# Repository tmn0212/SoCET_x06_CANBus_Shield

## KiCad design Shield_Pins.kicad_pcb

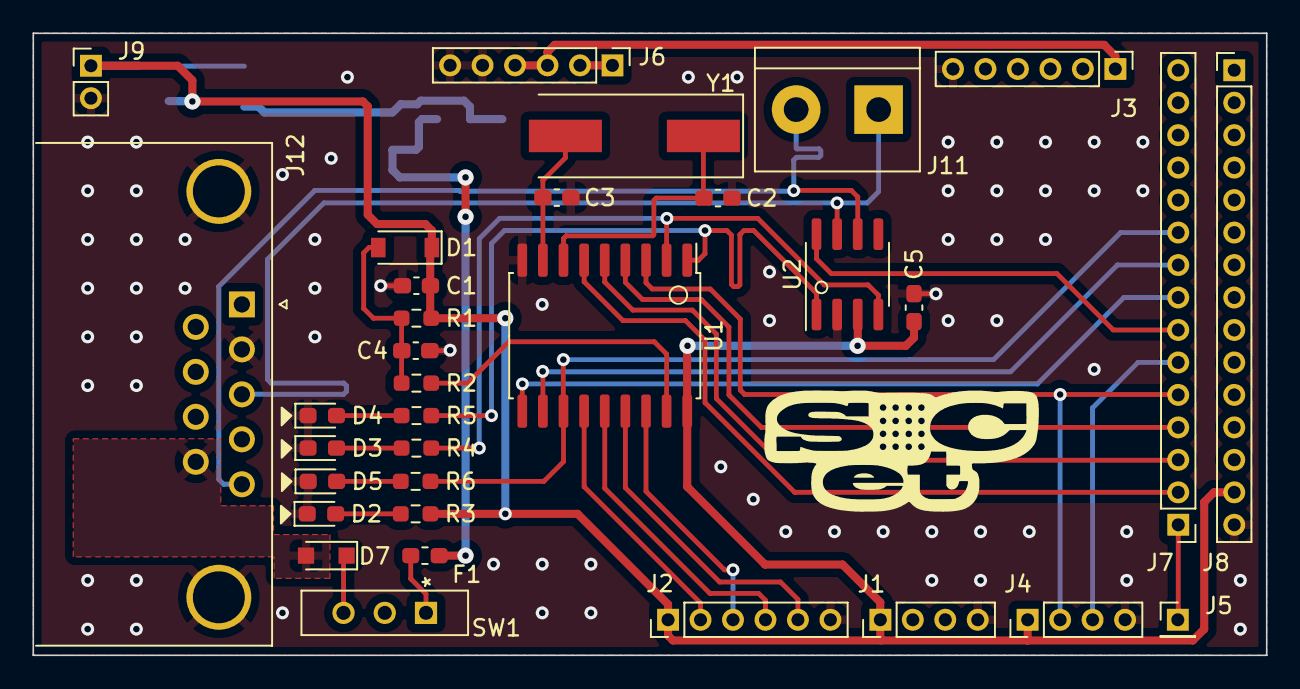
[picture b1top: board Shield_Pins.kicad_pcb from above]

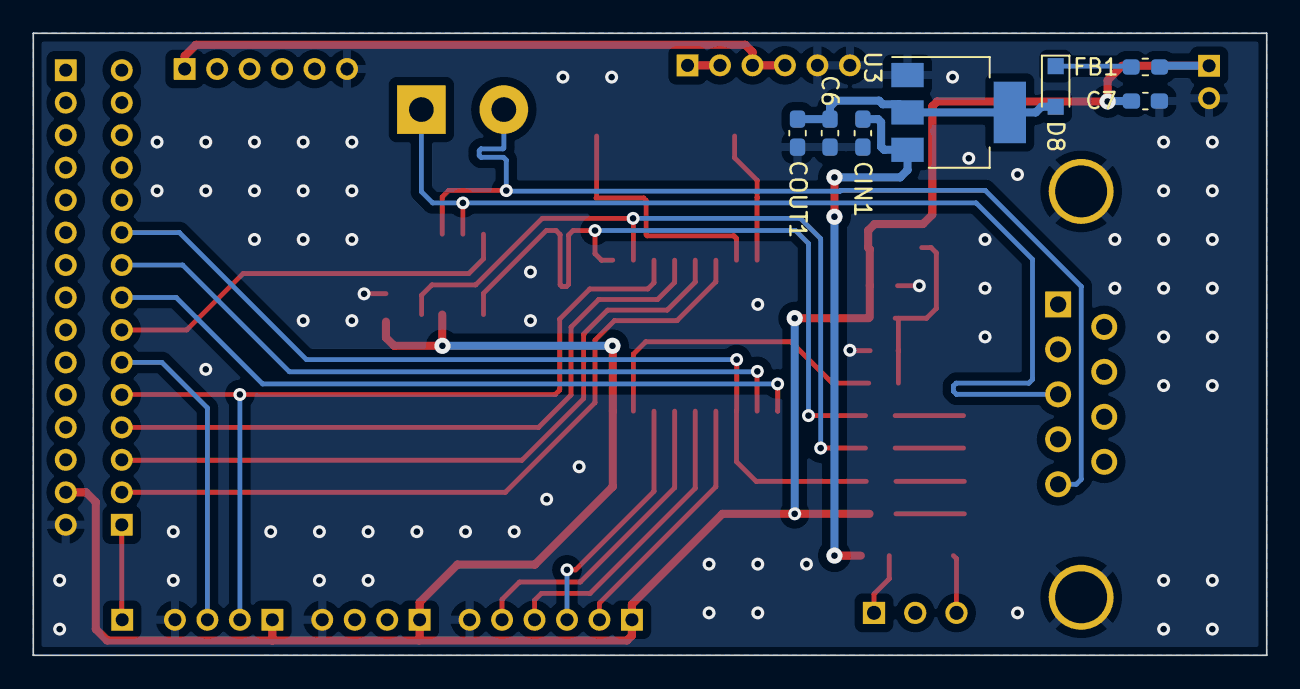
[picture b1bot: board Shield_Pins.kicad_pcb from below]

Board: 2 copper layers, 76.0 x 38.3 mm, 40 parts (7 on the bottom side), 36 nets.

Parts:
C1, C5: 0.1uF; C_0603_1608Metric_Pad1.08x0.95mm_HandSolder
C2, C3: 22pF; C_0603_1608Metric_Pad1.08x0.95mm_HandSolder
C4: 100pF; C_0603_1608Metric_Pad1.08x0.95mm_HandSolder
C6, C7: 100nF; C_0603_1608Metric_Pad1.08x0.95mm_HandSolder
CIN1: 100nF; C_0603_1608Metric_Pad1.08x0.95mm_HandSolder
COUT1: 10uF; C_0603_1608Metric_Pad1.08x0.95mm_HandSolder
D1: 3.3V 500mW; D_SOD-123
D2, D3, D4, D5: LED; LED_0603_1608Metric_Pad1.05x0.95mm_HandSolder
D7, D8: BAT165AX; D_SOD-323_HandSoldering
F1: 1.5A Fuse; Fuse_0603_1608Metric_Pad1.05x0.95mm_HandSolder
FB1: 120R; L_0603_1608Metric_Pad1.05x0.95mm_HandSolder
J1, J4: Conn_01x04_Male; PinHeader_1x04_P2.00mm_Vertical
J2, J3, J6: Conn_01x06_Male; PinHeader_1x06_P2.00mm_Vertical
J5: Conn_01x01_Male; PinHeader_1x01_P2.00mm_Vertical
J7, J8: Conn_01x15_Male; PinHeader_1x15_P2.00mm_Vertical
J9: Conn_01x02_Male; PinHeader_1x02_P2.00mm_Vertical
J11: Screw_Terminal_01x02; TerminalBlock_bornier-2_P5.08mm
J12: DB9_Male; DSUB-9_Male_Horizontal_P2.77x2.84mm_EdgePinOffset9.90mm_Hou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
R1: 6.3kR; R_0603_1608Metric_Pad0.98x0.95mm_HandSolder
R2: 1kR; R_0603_1608Metric_Pad0.98x0.95mm_HandSolder
R3, R4, R5, R6: 100R; R_0603_1608Metric_Pad0.98x0.95mm_HandSolder
SW1: SW_SPDT; 09.03290.01 switch
U1: MCP2515-xSO; SOIC-18W_7.5x11.6mm_P1.27mm
U2: MCP2551-I-SN; SOIC-8_3.9x4.9mm_P1.27mm
U3: LD1117S50TR_SOT223; SOT-223-3_TabPin2
Y1: 8MHz Crystal; Crystal_SMD_HC49-SD

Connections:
5V_OBD: C6.1, COUT1.1, D8.2 (A), U3.2 (VO)
12V_OBD: CIN1.1, F1.2, U3.3 (VI)
12V_OBD_IN: D7.2 (A), J12.9
+1V8: J6.1, J6.2
+3.3V: J3.1, J6.3, J6.4
+5V: C1.1, C5.1, C7.1, D1.1 (K), FB1.2, J1.1, J2.1, J4.1, J8.14, J9.1, R1.1, R3.1, U1.18 (VDD), U2.3 (VDD)
CANH: J11.1, J12.3, U2.7 (CANH)
CANL: J11.2, J12.5, U2.6 (CANL)
GND: C1.2, C2.2, C3.2, C4.2, C5.2, C6.2, C7.2, CIN1.2, COUT1.2, D2.1 (K), D3.1 (K), D4.1 (K), D5.1 (K), J1.4, J2.6, J3.6, J4.4, J6.5, J6.6, J8.15, J9.2, J12.2, U1.9 (VSS), U2.2 (VSS), U3.1 (GND)
IO7: J5.1, J7.1
IO8: J7.2, U1.6 (~TX2RTS)
IO9: J7.3, U1.5 (~TX1RTS)
IO10: J7.4, U1.4 (~TX0RTS)
IO11: J4.2, J7.5, U1.3 (CLKOUT/SOF)
IO12: J4.3, J7.6
IO17: J7.7, U2.8 (Rs)
IO18: J7.8, U1.10 (~RX1BF)
IO19: J7.9, U1.11 (~RX0BF)
IO20: J7.10, R6.1, U1.12 (~INT)
IO.CSB: J2.3, U1.16 (~CS)
IO.SCK: J2.2, U1.13 (SCK)
IO.SDI: J2.4, U1.14 (SI)
IO.SDO: J2.5, U1.15 (SO)
unnamed: C4.1, D1.2 (A), R1.2, R2.1
unnamed: D2.2 (A), R3.2
unnamed: D3.2 (A), R4.2
unnamed: D4.2 (A), R5.2
unnamed: D5.2 (A), R6.2
unnamed: D7.1 (K), SW1.2 (B)
unnamed: D8.1 (K), FB1.1
unnamed: F1.1, SW1.3 (C)
OSC1: C3.1, U1.8 (OSC1), Y1.2
OSC2: C2.1, U1.7 (OSC2), Y1.1
RXCAN: R4.1, U1.2 (RXCAN), U2.4 (RXD)
TXCAN: R5.1, U1.1 (TXCAN), U2.1 (TXD)
~CAN_RST: R2.2, U1.17 (~RESET)

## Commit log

2023-02-04 Init Push
2023-02-10 Complete Board (1)
2023-02-10 fix LED
2023-02-10 Update 3D Library
